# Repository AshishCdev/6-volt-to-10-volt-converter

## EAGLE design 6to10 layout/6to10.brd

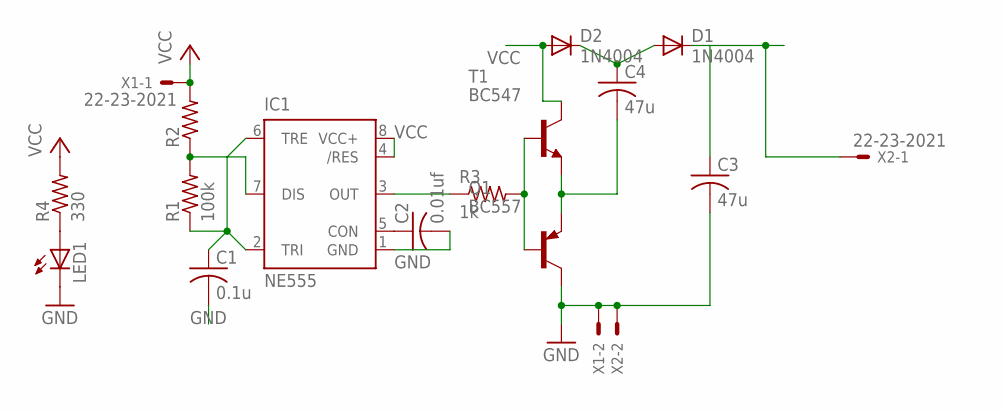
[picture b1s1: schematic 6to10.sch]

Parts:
C1: 0.1u; C050-025X075
C2: 0.01uf; C050-025X075
C3, C4: 47u; C050-075X075
D1, D2: 1N4004; DO41-10
IC1: NE555; DIL-08
LED1: LED5MM
Q1: BC557; TO92
R1: 100k; 0204/7
R2: R-US_0204/7; 0204/7
R3: 1k; 0204/7
R4: 330; 0204/7
T1: BC547; TO92
X1, X2: 22-23-2021

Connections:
GND: C1.2, C2.2, C3.2, IC1.1 (GND), LED1.K (C), Q1.3 (C), X1.2, X2.2
unnamed: C1.1, IC1.2 (TRI), IC1.6 (TRE), R1.1
unnamed: C2.1, IC1.5 (CON)
unnamed: IC1.7 (DIS), R1.2, R2.1
unnamed: IC1.3 (OUT), R3.1
unnamed: C4.1, D1.A, D2.C
unnamed: C3.1, D1.C, X2.1
unnamed: Q1.2 (B), R3.2, T1.2 (B)
unnamed: C4.2, Q1.1 (E), T1.1 (E)
unnamed: LED1.A, R4.1
VCC: D2.A, IC1.4 (/RES), IC1.8 (VCC+), R2.2, R4.2, T1.3 (C), X1.1

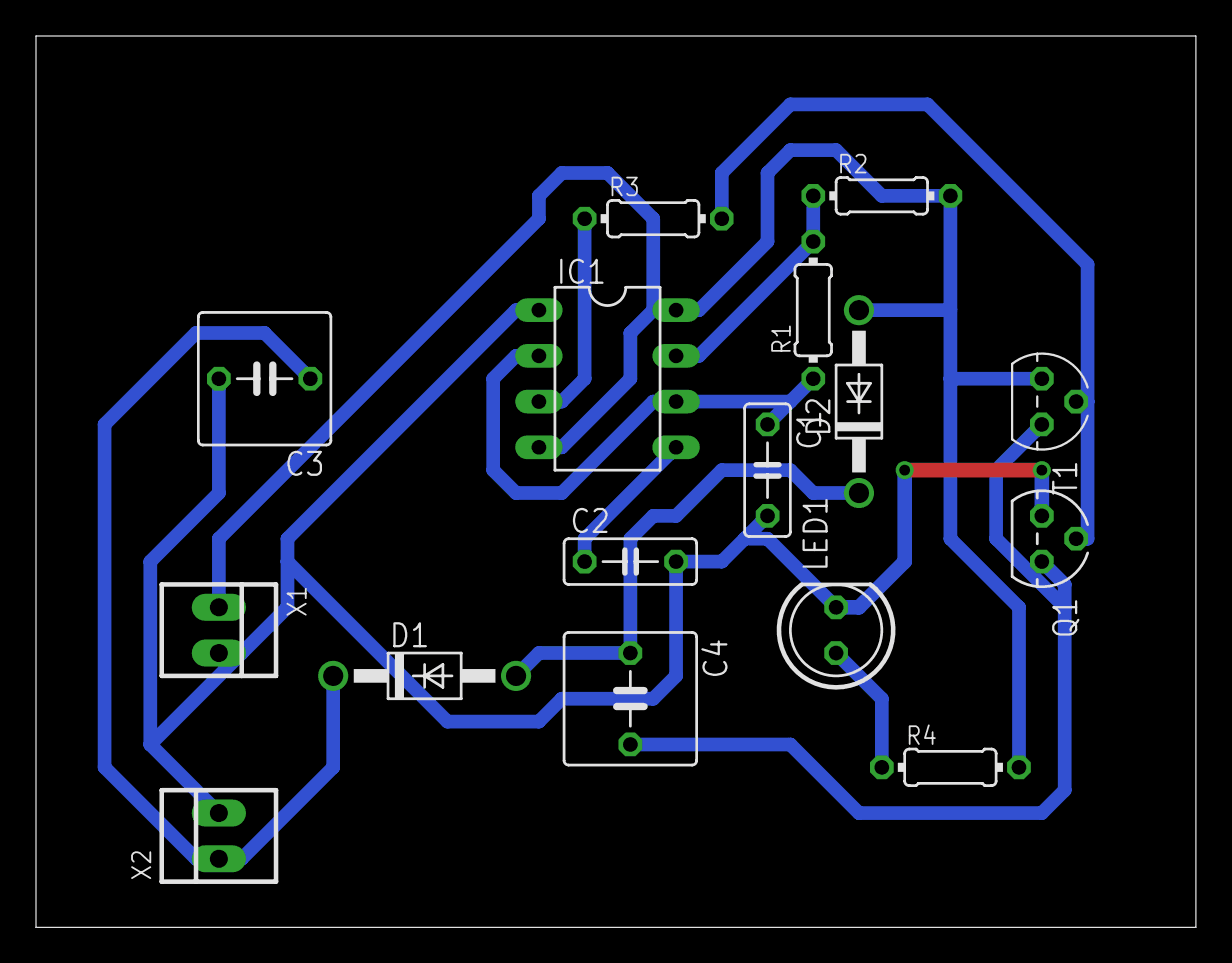
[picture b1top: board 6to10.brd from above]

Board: 2 copper layers, 64.4 x 49.5 mm, 16 parts (0 on the bottom side), 11 nets.

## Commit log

2016-01-01 Added schematic and layout, made in eagle
